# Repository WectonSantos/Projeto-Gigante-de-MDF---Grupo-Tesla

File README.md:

🛠️ Gigante de MDF – Projeto de Programação de Hardware 2025 - Grupo Tesla 

Projeto desenvolvido para a disciplina Programação de Hardware, utilizando o microcontrolador ATmega328P e envolvendo mecânica, eletrônica e firmware embarcado.

📌 Sobre o Projeto
O objetivo deste trabalho foi aplicar, na prática, os conteúdos estudados ao longo do semestre, criando um robô móvel (“Gigante de MDF”) capaz de:

• Locomover-se por meio de motores controlados via PWM
• Emitir feixes de laser vermelho (≤ 300 mW)
• Detectar impactos recebidos por lasers adversários
• Gerenciar um sistema de “vidas” por LEDs
• Realizar reações automáticas ao ser atingido

O foco principal do projeto foi o desenvolvimento do firmware, sem depender de shields prontos, bibliotecas externas não autorizadas ou soluções prontas da comunidade Arduino.

🚗 Estrutura Mecânica
O robô construído segue o conjunto de requisitos mecânicos:

• Dimensões máximas de 200 × 200 × 200 mm
• Sistema com 2 a 4 rodas, capaz de realizar movimentação no próprio eixo
• “Arma” laser posicionada no centro do robô, a 100 mm de altura
• Receptor de luz instalado ao lado direito da arma, com difusor de 20 mm
• Estrutura baseada em MDF, com cortes e montagem conforme projeto disponibilizado

🧠 Firmware e Programação
O firmware foi desenvolvido inteiramente do zero, com base no datasheet oficial da Microchip, sem bibliotecas prontas (exceto as eventualmente autorizadas pelo professor).
O código atende às seguintes especificações:

✔️ Microcontrolador
• ATmega328P
✔️ Requisitos de Programação
• Controle dos motores via PWM de hardware
• Laser temporizado por Timer
• Receptor de luz com rotina de interrupção
• Delay de segurança de 5s após cada acerto
• Gestão de LEDs e lógica de “vidas”
• Rotina de giro automático de 180°
• Reset de vidas via interrupção externa
• Código completamente documentado em Doxygen

📚 Documentação
A documentação completa do software foi gerada usando Doxygen e está disponível em:
/Documentacao/doxygen/

👥 Integrantes – Grupo Tesla
• Rafael Wippich
• Thiago Taveira
• Wecton Santos

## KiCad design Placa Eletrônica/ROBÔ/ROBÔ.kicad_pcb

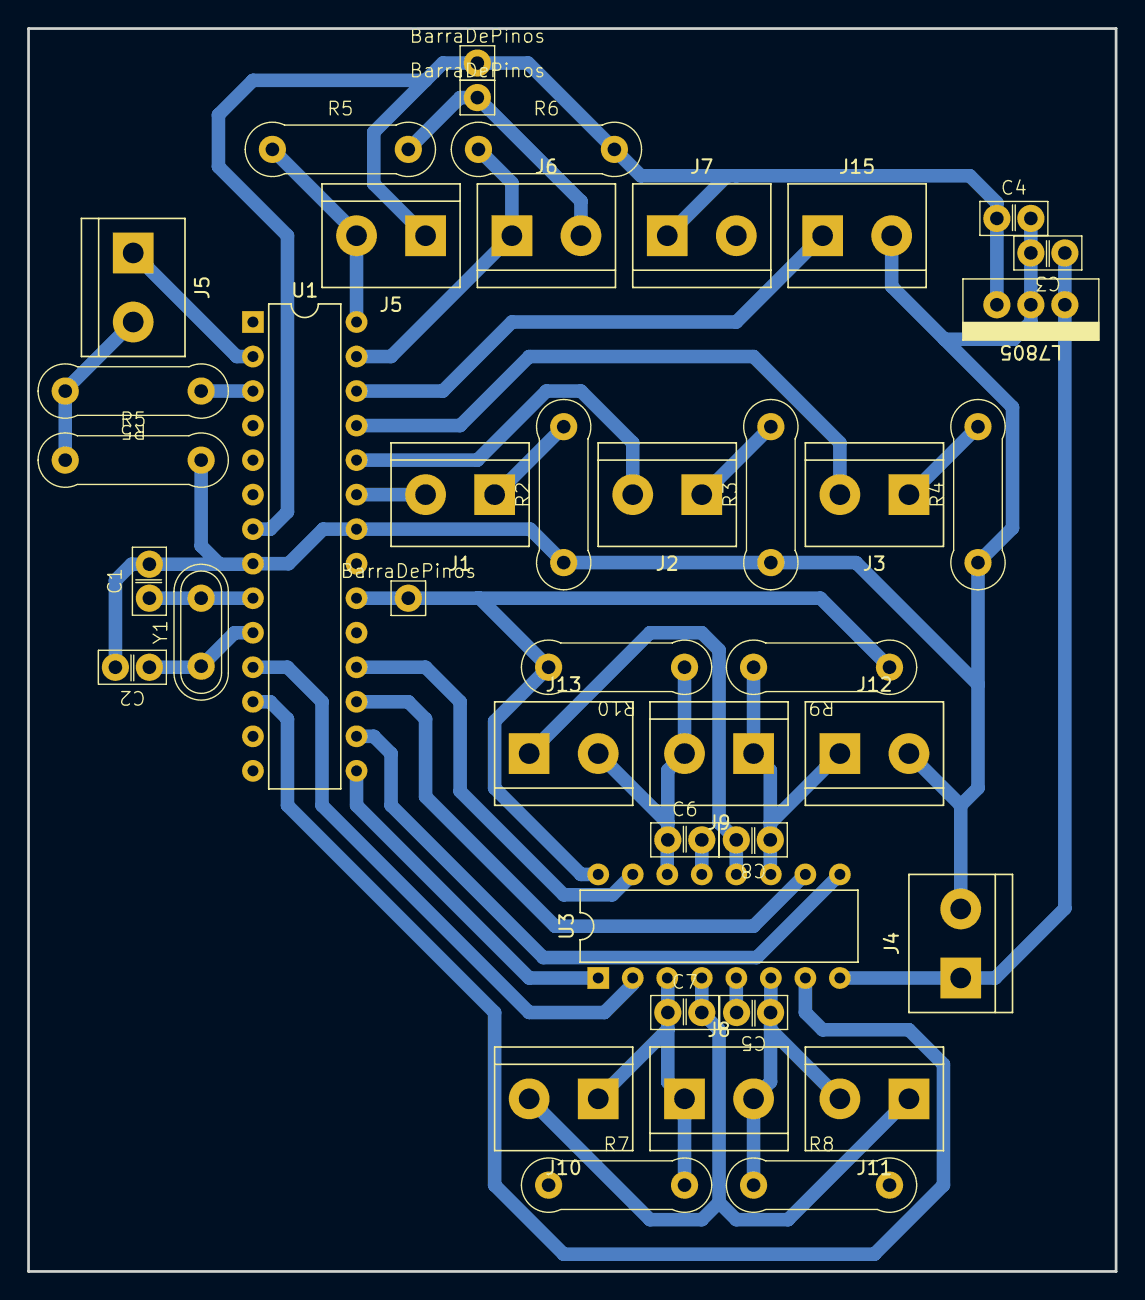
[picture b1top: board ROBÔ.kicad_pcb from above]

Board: 2 copper layers, 80.0 x 91.4 mm, 41 parts (0 on the bottom side), 27 nets.

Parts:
BarraDePinos: DistânciaEntreFuros:_2,54mm; BarraDePinos
BarraDePinos#2, BarraDePinos#3: DistânciaEntreFuros:_2,54mm; BarraDePinos
C1, C2, C3, C4, C5, C6, C7, C8: C; CapacitorCerâmico-100nF_ou_0,1uF
J1, J2, J3, J4, J5, J5#2, J6, J7, J8, J9, J10, J11, J12, J13, J15: Screw_Terminal_01x02; TerminalBlock_bornier-2_P5.08mm
R2, R3, R4, R5, R5#2, R5#3, R6, R7, R8, R9, R10: R; Resistor
U1: ATmega328-P; DIP-28_W7.62mm
U2: L7805; ReguladorDeTensão-L7805_5V
U3: L293D; DIP-16_W7.62mm
Y1: Crystal; CristalOscilador16MHz

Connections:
5v: BarraDePinos#2.1, BarraDePinos#3.1, C4.IN, J5.1, J7.1, R6.2, R7.1, R8.2, R9.1, R10.2, U1.7 (VCC), U1.20 (AVCC), U2.OUTPUT, U3.16 (VCC1)
9v: C3.IN, J4.1, U2.INPUT, U3.8 (VCC2)
Crystal I: C1.IN, U1.9 (XTAL1/PB6), Y1.2
Crystal II: C2.IN, U1.10 (XTAL2/PB7), Y1.1
GND: BarraDePinos.1, C1.GND, C2.GND, C3.GND, C4.GND, C5.GND, C6.GND, C7.GND, C8.GND, J4.2, J6.2, J10.2, J11.1, J12.2, J13.1, J15.2, R2.1, R3.1, R4.1, R5#2.2, R5#3.2, U1.8 (GND), U1.22 (GND), U2.GND, U3.4 (GND), U3.5 (GND), U3.12 (GND), U3.13 (GND)
In 1 Motor 1: U1.11 (PD5), U3.2 (1A)
In 1 Motor 2: U1.17 (PB3), U3.10 (3A)
In 2 Motor 1: U1.12 (PD6), U3.7 (2A)
In 2 Motor 2: U1.18 (PB4), U3.15 (4A)
LDR: J5.2, R5#2.1, U1.28 (PC5)
Laser: J15.1, U1.26 (PC3)
Led 1: J1.2, U1.23 (PC0)
Led 2: J2.2, U1.24 (PC1)
Led 3: J3.2, U1.25 (PC2)
unnamed: J1.1, R2.2
unnamed: J2.1, R3.2
unnamed: J3.1, R4.2
Out 1 Motor 1: C7.IN, J8.1, J10.1, R7.2, U3.3 (1Y)
Out 1 Motor 2: C8.IN, J9.1, J12.1, R9.2, U3.11 (3Y)
Out 2 Motor 1: C5.IN, J8.2, J11.2, R8.1, U3.6 (2Y)
Out 2 Motor 2: C6.IN, J9.2, J13.2, R10.1, U3.14 (4Y)
PWM Motor 1: U1.15 (PB1), U3.1 (EN1,2)
PWM Motor 2: U1.16 (PB2), U3.9 (EN3,4)
RX: J5#2.1, U1.2 (PD0)
Sensor IV: J6.1, R6.1, U1.27 (PC4)
TX: R5.1, U1.3 (PD1)
Temp: J5#2.2, R5.2, R5#3.1

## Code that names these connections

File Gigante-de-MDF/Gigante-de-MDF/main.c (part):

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
// ROTINA QUE CONFIGURA OS LEDS DE VIDA
void ledsVida(){
	DDRC |= (1 << PC0); // LED 1 (SAÍDA)
	DDRC |= (1 << PC1); // LED 2 (SAÍDA)
	DDRC |= (1 << PC2); // LED 3 (SAÍDA)
	
	PORTC |= (1<< PC0); // LIGANDO LED 1
	PORTC |= (1<< PC1); // LIGANDO LED 1
	PORTC |= (1<< PC2); // LIGANDO LED 1
}
// ROTINA QUE CONFIGURA OS MOTORES
void motores() {
	DDRB |= (1<<PB1) | (1<<PB2) | (1<<PB3) | (1<<PB4);
	DDRD |= (1<<PD5) | (1<<PD6);

	// Desliga tudo ANTES de qualquer comando Bluetooth
	PORTB &= ~((1<<PB1)|(1<<PB2)|(1<<PB3)|(1<<PB4));
	OCR0A = 0;
	OCR0B = 0;
}
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
// BOTÕES PREVIAMENTE QUE SERÃO TROCADOS PELO VALOR RECEBIDO DO CONTROLE
void botoes(){
	DDRB &= ~(1 << PB6);
	DDRB &= ~(1 << PB0);
	DDRD &= ~(1 << PD4);
}

// ROTINA QUE CONFIGURA O LASER
void laser(){
	DDRC |= (1 << PC3); // LASER PORTA C3 (CTC)
}

// ROTINA LDR
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
	ADCSRA = (1 << ADEN) | (1 << ADPS2) | (1 << ADPS1) | (1 << ADPS0); // prescaler 128 (16MHz/128=125kHz)
	//DIDR0 = (1 << ADC4D);
	//DDRC &= ~(1 << PC4); 
}

uint16_t adc_read(uint8_t canal) {
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
void atualizaLedsVida() {
	if (vidas >= 3){
		PORTC |= (1 << PC0) | (1 << PC1) | (1 << PC2);
	}else if (vidas == 2) {
		PORTC |= (1 << PC1) | (1 << PC2);
		PORTC &= ~(1 << PC0);
	}else if (vidas == 1) {
		PORTC |= (1 << PC2);
		PORTC &= ~((1 << PC0) | (1 << PC1));
	}else{
		PORTC &= ~((1 << PC0) | (1 << PC1) | (1 << PC2));
		fimDeJogo = 1;
	}
}
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// ROTINA DOS MOTORES
void ligaMotoresHorario(){		
    // Motor esquerdo horário
    PORTB |=  (1<<PB1);
    PORTB &= ~(1<<PB2);

    // Motor direito horário
    PORTB |=  (1<<PB3);
    PORTB &= ~(1<<PB4);
}

void ligaMotoresAntiHorario(){
    // Motor esquerdo anti-horário
    PORTB |=  (1<<PB2);
    PORTB &= ~(1<<PB1);

    // Motor direito anti-horário
    PORTB |=  (1<<PB4);
    PORTB &= ~(1<<PB3);
}

void giraEsquerda() {
    // Motor esquerdo anti-horário
    PORTB |=  (1<<PB2);
    PORTB &= ~(1<<PB1);

    // Motor direito horário
    PORTB |=  (1<<PB3);
    PORTB &= ~(1<<PB4);
}

void giraDireita() {
    // Motor esquerdo horário
    PORTB |=  (1<<PB1);
    PORTB &= ~(1<<PB2);

    // Motor direito anti-horário
    PORTB |=  (1<<PB4);
    PORTB &= ~(1<<PB3);
}

void girar360() {
	// Motor 1 horário: IN1=1, IN2=0
	PORTB |=  (1<<PB1);
	PORTB &= ~(1<<PB2);

	// Motor 2 anti-horário: IN3=0, IN4=1
	PORTB &= ~(1<<PB3);
	PORTB |=  (1<<PB4);

	// PWM
	OCR0A = 200;  // motor 2
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

void curvaDireita(){
	PORTB |= (1<<PB1)|(1<<PB3);
	PORTB &= ~((1<<PB2)|(1<<PB4));	
	// LIGA PWM
	OCR0A = 255;
	OCR0B = 77;
}
void curvaEsquerda(){
	PORTB |= (1<<PB1)|(1<<PB3);
	PORTB &= ~((1<<PB2)|(1<<PB4));
	// LIGA PWM
	OCR0A = 77;
	OCR0B = 255;
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void pararMotores() {
	OCR0A = 0;
	OCR0B = 0;
	PORTB &= ~((1<<PB1)|(1<<PB2)|(1<<PB3)|(1<<PB4));
}


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	}
	else if (PINB & (1 << PB0)) {
		ligaMotoresAntiHorario();
	}//else if (PINB & (1 << PB6)){
		//ligaMotoresMeiaForca();  
	//}
	else {
		OCR0A = 0;
		OCR0B = 0;
		PORTB &= ~((1 << PB7) | (1 << PB5) | (1 << PB4) | (1 << PB0));
	}	
}
//FIM ROTINA DOS MOTORES
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// PISCA LASER SE ESTIVER EM MODO NORMAL == SEM BLOQUEIO
ISR(TIMER1_COMPA_vect) {
	if (estado == 0){
		PORTC ^= (1 << PC3);
	}
	//PORTC ^= (1 << PC3);  // ALTERNA ESTADO DO LED
}

// TICKS DE 1 MS PARA GERENCIAR A SEQUÊNCIA SEM DELAY
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		if (contador >= 1000) {
			// APÓS O GIRO PARA MOTORES, DESLIGA LASER, INICIA BLOQUEIO
			pararMotores(); 
			PORTC &= ~(1 << PC3);// DESLIGA LASER
			timer1_stop(); // GARANTE QUE O TIMER1 NÃO VAI MAIS PISCAR
			estado = 2; // ALTERNA PARA O ESTADO DE BLOQUEIO
			contador = 0; 
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			contador = 0;
			seqRequisitada = 0;
			timer1_init(); // REATIVA O PISCA DO LASER
			PORTC &= ~(1 << PC3);
			timer2_stop();
		}
	}
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	while(1){
		pararMotores();
		estado = 2;
		PORTC &= ~(1 << PC3);// DESLIGA LASER
		timer1_stop(); // GARANTE QUE O TIMER1 NÃO VAI MAIS PISCAR
	}
}
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	UART_Init();
	
    // GARANTE SAÍDAS LIMPAS
	PORTB &= ~((1 << PB1) | (1 << PB2) | (1 << PB3) | (1 << PB4));	
	
	// RESET
	
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    while (1) 
    {
		//ROTINA LDR
		valorLDR = adc_read(5); // LÊ O ADC5 (PC5)
		// debug ldr
		UART_SendString("LDR = ");
		UART_SendInt(valorLDR);
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		// debug ldr

		if (valorLDR > 100) {
			luzAlta = 1; // LDR RECEBEU VALOR ALTO
			executaPedidoSequencia();
		}else{
			luzAlta = 0;
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		// SOMENTE ACEITA CONTROLES QUANDO NÃO ESTIVER EM BLOQUEIO
        if (estado == 0){
			verificaSentido();
			if (PINB & (1 << PB6)){
		        executaPedidoSequencia();
				vidas--;
	        }			
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
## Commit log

2025-11-27 Update README with project details and specifications
    Added detailed project description, objectives, mechanical structure, firmware specifications, and team members.
2025-11-27 correção bug não girar 360
2025-11-27 reset
2025-11-28 Fix project title formatting in README.md
    Fixed formatting issue in project title.
2025-11-28 Fix capitalization in README.md
    Corrected capitalization in documentation path and project title.
2025-11-28 Fix spelling of microcontroller in README
    Corrected spelling of 'ATMega328' to 'ATmega328P' in the README.
2025-11-28 add placa
2025-11-29 restart no controle
2025-11-29 doxy
2025-12-11 correcao ldr
2025-12-13 att p3
